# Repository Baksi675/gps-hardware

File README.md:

# GPS Tracking Device — Hardware

An electronic device built for GPS tracking. The project was made with KiCad.

For the firmware repository visit gps-firmware: https://github.com/Baksi675/gps-firmware

---

## Features

- STM32F401RE microcontroller.
- 32.768 kHz crystal oscillator for the internal RTC of the microcontroller.
- USB micro B connector to power the board and to provide USB based host - target runtime communication.
- USBLC6-2SC6 ESD protection diode network to protect the USB connector from ESD events.
- CH340C USB-UART converter IC to provide communication capabilities between host and target with a USB cable.
- LD30950PU33R LDO for 5 V to 3.3 V conversion.
- u-blox NEO-6M GPS module connected to the microcontroller via UART.
- U.FL antenna connector for the ceramic patch antenna.
- 3 V CR2032 coin cell for the internal RTC of the microcontroller.
- microSD card slot connected to the microcontroller via SPI.
- Three user button connectors.
- A 4 pin connector for the display (I2C).
- A 5 pin debug connector (SWD).
- A connector for an external GPS module in case the on-board module is not operational (UART).

---

## Demonstration playlist

https://www.youtube.com/watch?v=A6QJqgy0O1o&list=PLb_bXLsinHOQtkZ2X2QlIw-E_5eapHqGd

---

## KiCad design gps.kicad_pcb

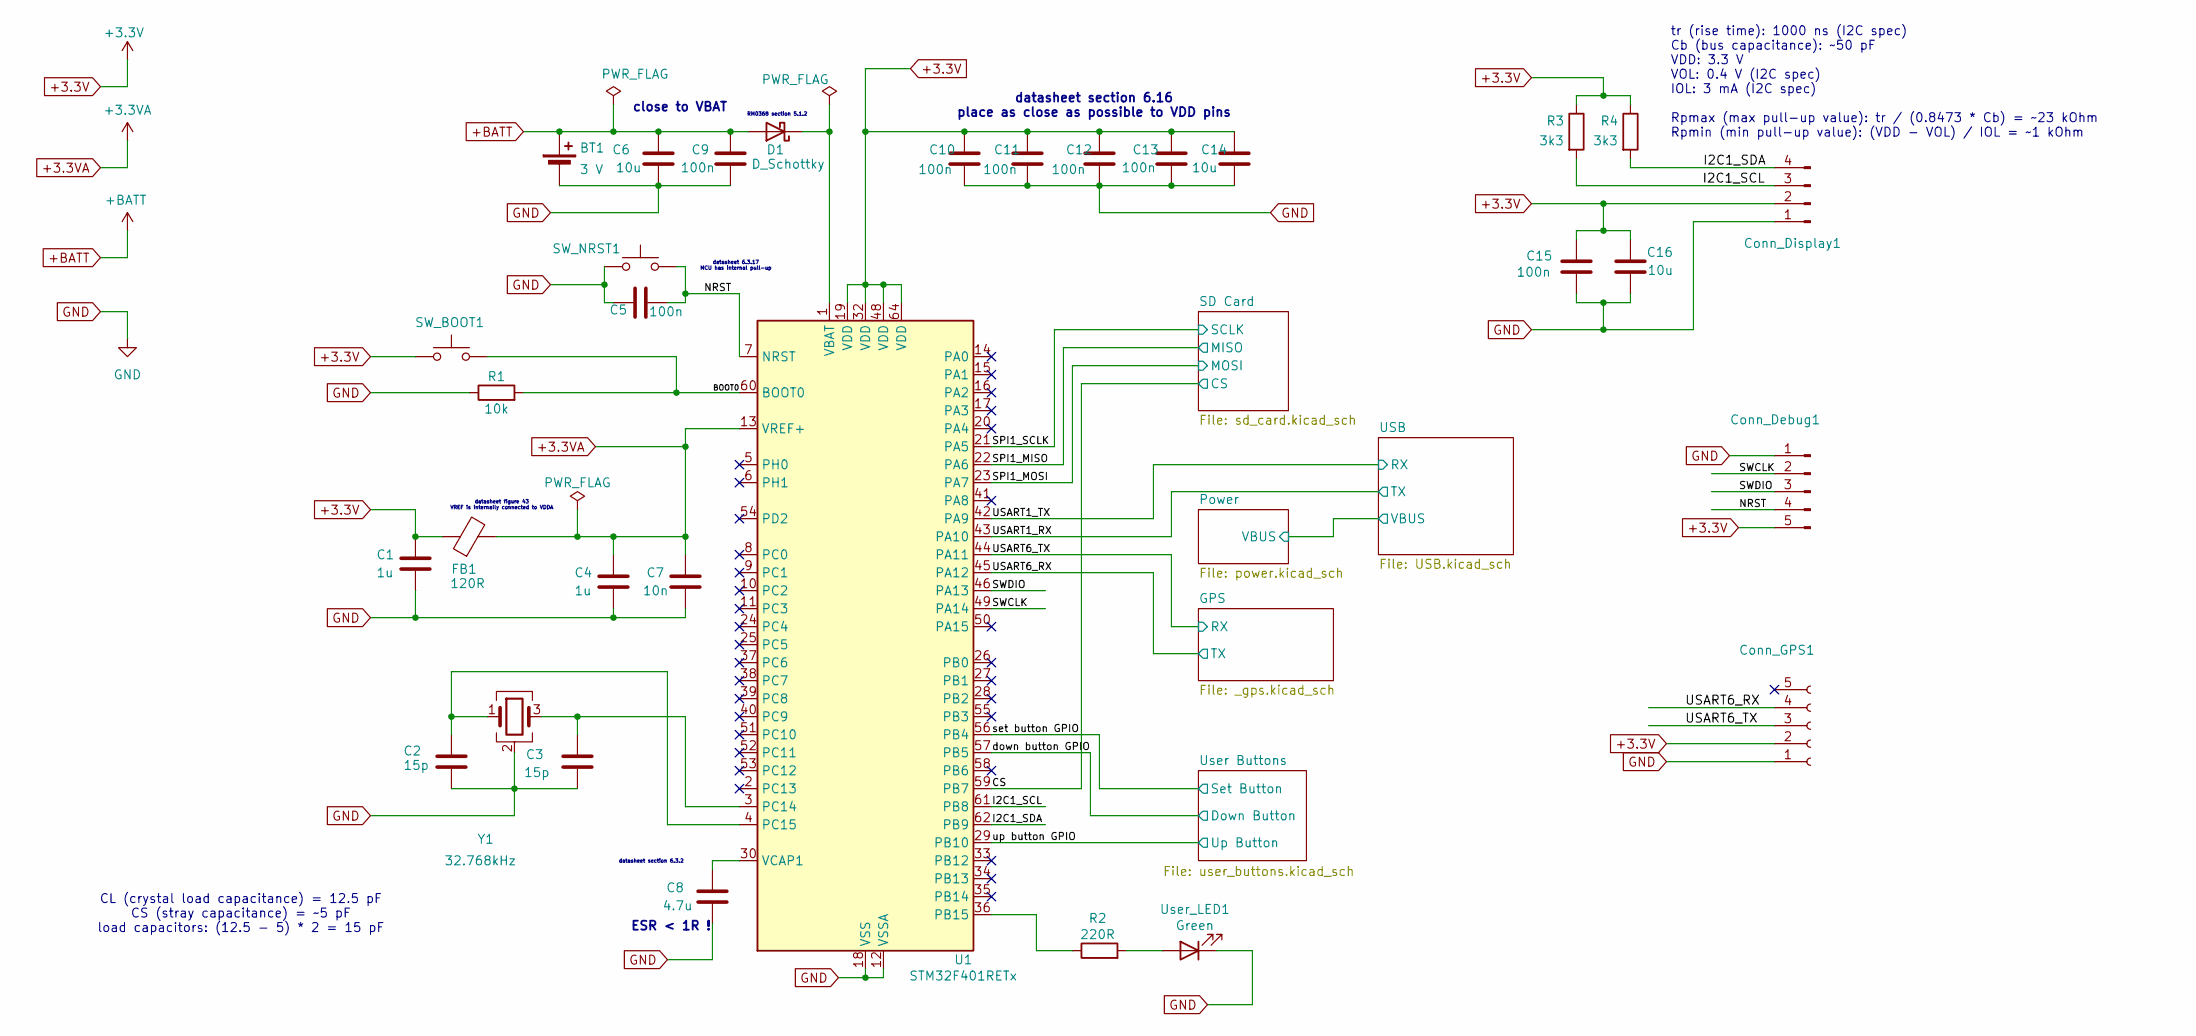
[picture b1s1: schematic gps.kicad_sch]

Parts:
BT1: 3 V; BatteryHolder_MYOUNG_BS-07-A1BJ001_CR2032
C1, C4: 1u; C_0603_1608Metric
C2, C3: 15p; C_0603_1608Metric
C5, C9, C10, C11, C12, C13, C15: 100n; C_0402_1005Metric
C6, C14, C16: 10u; C_0603_1608Metric
C7: 10n; C_0402_1005Metric
C8: 4.7u; C_0603_1608Metric
Conn_Debug1: Conn_01x05_Pin; PinHeader_1x05_P2.54mm_Vertical
Conn_Display1: Conn_01x04_Pin; PinHeader_1x04_P2.54mm_Vertical
Conn_GPS1: Conn_01x05_Socket; PinSocket_1x05_P2.54mm_Vertical
D1: D_Schottky; D_0603_1608Metric
FB1: 120R; L_0603_1608Metric
R1: 10k; R_0402_1005Metric
R2: 220R; R_0402_1005Metric
R3, R4: 3k3; R_0402_1005Metric
SW_BOOT1: SW_Push; SW_Push_1P1T_NO_E-Switch_TL3301NxxxxxG
SW_NRST1: SW_Push; SW_Push_1P1T_NO_E-Switch_TL3301NxxxxxG
U1: STM32F401RETx; LQFP-64_10x10mm_P0.5mm
User_LED1: Green; LED_0603_1608Metric
Y1: 32.768kHz; Crystal_SMD_SeikoEpson_MC306-4Pin_8.0x3.2mm

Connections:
+3.3V: C1.1, C10.1, C11.1, C12.1, C13.1, C14.1, C15.2, C16.2, Conn_Debug1.5, Conn_Display1.2, Conn_GPS1.2, FB1.1, R3.1, R4.1, SW_BOOT1.1, U1.19 (VDD), U1.32 (VDD), U1.48 (VDD), U1.64 (VDD); also elsewhere on the board
+3.3VA: C4.1, C7.1, FB1.2, U1.13 (VREF+)
+BATT: BT1.1 (+), C6.1, C9.1, D1.2 (A); also elsewhere on the board
/BOOT0: R1.2, SW_BOOT1.2, U1.60 (BOOT0)
/CS: U1.59 (PB7); also elsewhere on the board
/I2C1_SCL: Conn_Display1.3, R3.2, U1.61 (PB8)
/I2C1_SDA: Conn_Display1.4, R4.2, U1.62 (PB9)
/NRST: C5.2, Conn_Debug1.4, SW_NRST1.2, U1.7 (NRST)
/SPI1_MISO: U1.22 (PA6); also elsewhere on the board
/SPI1_MOSI: U1.23 (PA7); also elsewhere on the board
/SPI1_SCLK: U1.21 (PA5); also elsewhere on the board
/SWCLK: Conn_Debug1.2, U1.49 (PA14)
/SWDIO: Conn_Debug1.3, U1.46 (PA13)
/USART1_RX: U1.43 (PA10); also elsewhere on the board
/USART1_TX: U1.42 (PA9); also elsewhere on the board
/USART6_RX: Conn_GPS1.4, U1.45 (PA12); also elsewhere on the board
/USART6_TX: Conn_GPS1.3, U1.44 (PA11); also elsewhere on the board
/down button GPIO: U1.57 (PB5); also elsewhere on the board
/set button GPIO: U1.56 (PB4); also elsewhere on the board
/up button GPIO: U1.29 (PB10); also elsewhere on the board
GND: BT1.2 (-), C1.2, C2.2, C3.2, C4.2, C5.1, C6.2, C7.2, C8.2, C9.2, C10.2, C11.2, C12.2, C13.2, C14.2, C15.1, C16.1, Conn_Debug1.1, Conn_Display1.1, Conn_GPS1.1, R1.1, SW_NRST1.1, U1.12 (VSSA), U1.18 (VSS), U1.31 (VSS), U1.47 (VSS), U1.63 (VSS), User_LED1.1 (K), Y1.2 (G), Y1.4 (G); also elsewhere on the board
unnamed: D1.1 (K), U1.1 (VBAT)
unnamed: R2.1, U1.36 (PB15)
unnamed: C3.1, U1.3 (PC14), Y1.3
unnamed: C2.1, U1.4 (PC15), Y1.1
unnamed: C8.1, U1.30 (VCAP1)
unnamed: R2.2, User_LED1.2 (A)

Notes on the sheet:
CL (crystal load capacitance) = 12.5 pF CS (stray capacitance) = ~5 pF load capacitors: (12.5 - 5) * 2 = 15 pF
close to VBAT
datasheet figure 43 VREF is internally connected to VDDA
ESR < 1R !
datasheet section 6.3.2
datasheet section 6.16 place as close as possible to VDD pins
tr (rise time): 1000 ns (I2C spec) Cb (bus capacitance): ~50 pF VDD: 3.3 V VOL: 0.4 V (I2C spec) IOL: 3 mA (I2C spec) Rpmax (max pull-up value): tr / (0.8473 * Cb) = ~23 kOhm Rpmin (min pull-up value): (VDD - VOL) / IOL = ~1 kOhm
RM0368 section 5.1.2
datasheet 6.3.17 MCU has internal pull-up

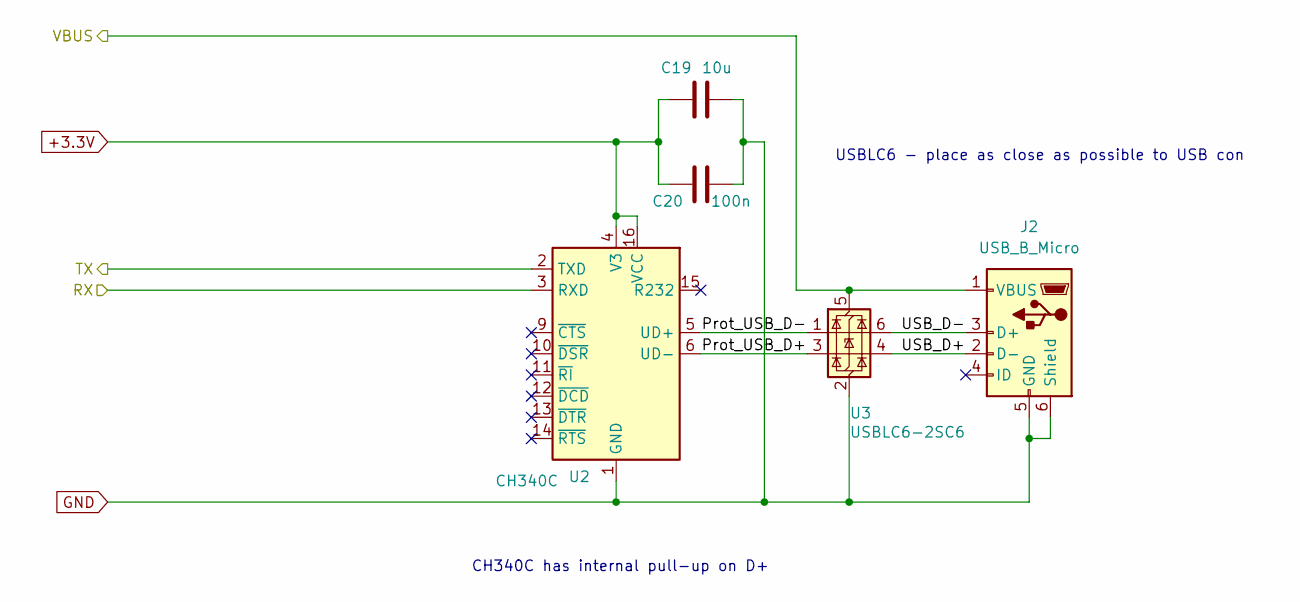
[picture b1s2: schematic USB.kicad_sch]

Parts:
C19: 10u; C_0603_1608Metric
C20: 100n; C_0402_1005Metric
J2: USB_B_Micro; USB_Micro-B_Amphenol_10118194-0001LF_Horizontal
U2: CH340C; SOIC-16_3.9x9.9mm_P1.27mm
U3: USBLC6-2SC6; SOT-23-6

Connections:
+3.3V: C19.1, C20.1, U2.4 (V3), U2.16 (VCC); also elsewhere on the board
/Power/VBUS: J2.1 (VBUS), U3.5 (VBUS); also elsewhere on the board
/USART1_RX: U2.2 (TXD); also elsewhere on the board
/USART1_TX: U2.3 (RXD); also elsewhere on the board
/USB/Prot_USB_D+: U2.6 (UD-), U3.3 (I/O2)
/USB/Prot_USB_D-: U2.5 (UD+), U3.1 (I/O1)
/USB/USB_D+: J2.2 (D-), U3.4 (I/O2)
/USB/USB_D-: J2.3 (D+), U3.6 (I/O1)
GND: C19.2, C20.2, J2.5 (GND), J2.6 (Shield), U2.1 (GND), U3.2 (GND); also elsewhere on the board

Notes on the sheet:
CH340C has internal pull-up on D+
USBLC6 - place as close as possible to USB con

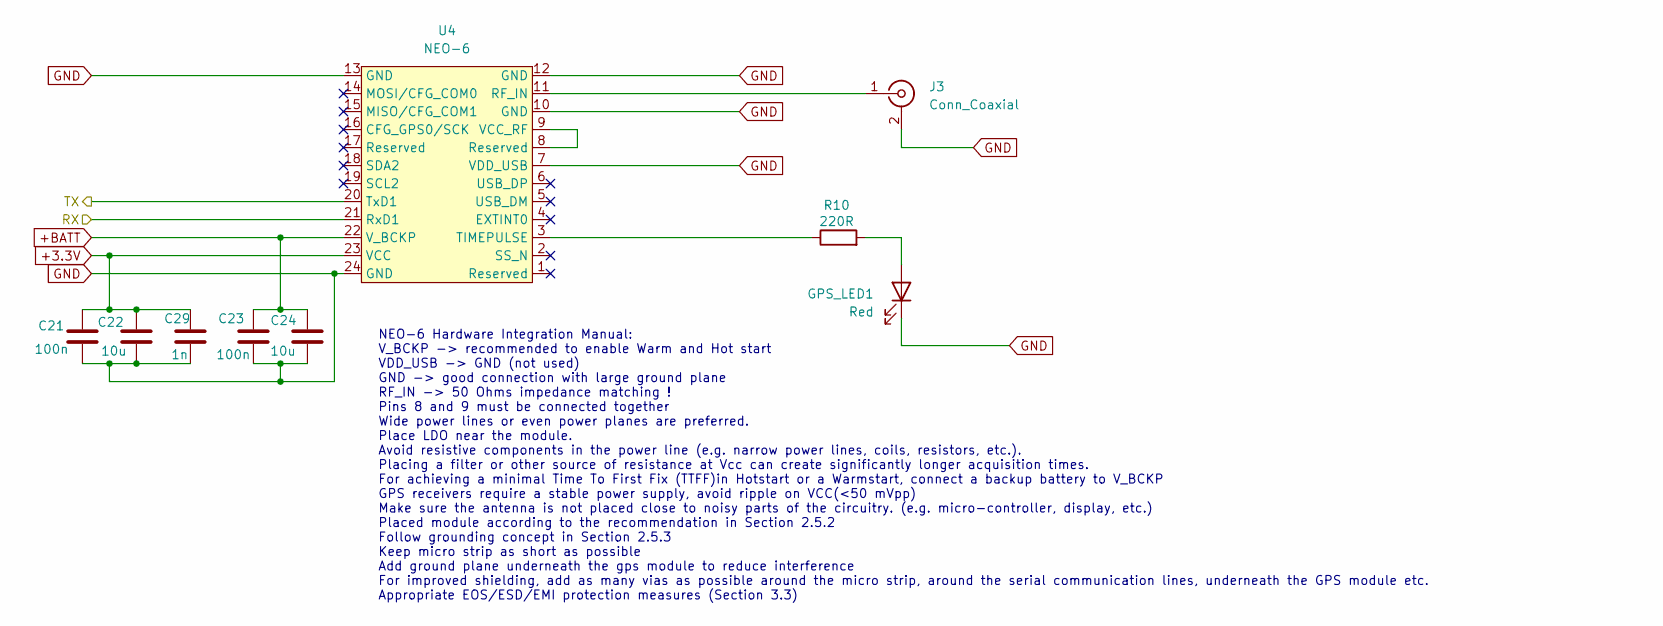
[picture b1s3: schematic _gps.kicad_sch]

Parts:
C21, C23: 100n; C_0402_1005Metric
C22, C24: 10u; C_0603_1608Metric
C29: 1n; C_0402_1005Metric
GPS_LED1: Red; LED_0603_1608Metric
J3: Conn_Coaxial; U.FL_Hirose_U.FL-R-SMT-1_Vertical
R10: 220R; R_0402_1005Metric
U4: NEO-6; ublox_NEO

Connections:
+3.3V: C21.1, C22.1, C29.1, U4.23 (VCC); also elsewhere on the board
+BATT: C23.1, C24.1, U4.22 (V_BCKP); also elsewhere on the board
/USART6_RX: U4.20 (TxD1); also elsewhere on the board
/USART6_TX: U4.21 (RxD1); also elsewhere on the board
GND: C21.2, C22.2, C23.2, C24.2, C29.2, GPS_LED1.1 (K), J3.2 (Ext), U4.7 (VDD_USB), U4.10 (GND), U4.12 (GND), U4.13 (GND), U4.24 (GND); also elsewhere on the board
unnamed: GPS_LED1.2 (A), R10.2
unnamed: J3.1 (In), U4.11 (RF_IN)
unnamed: R10.1, U4.3 (TIMEPULSE)
unnamed: U4.8 (Reserved), U4.9 (VCC_RF)

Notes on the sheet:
NEO-6 Hardware Integration Manual: V_BCKP -> recommended to enable Warm and Hot start VDD_USB -> GND (not used) GND -> good connection with large ground plane RF_IN -> 50 Ohms impedance matching ! Pins 8 and 9 must be connected together Wide power lines or even power planes are preferred. Place LDO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

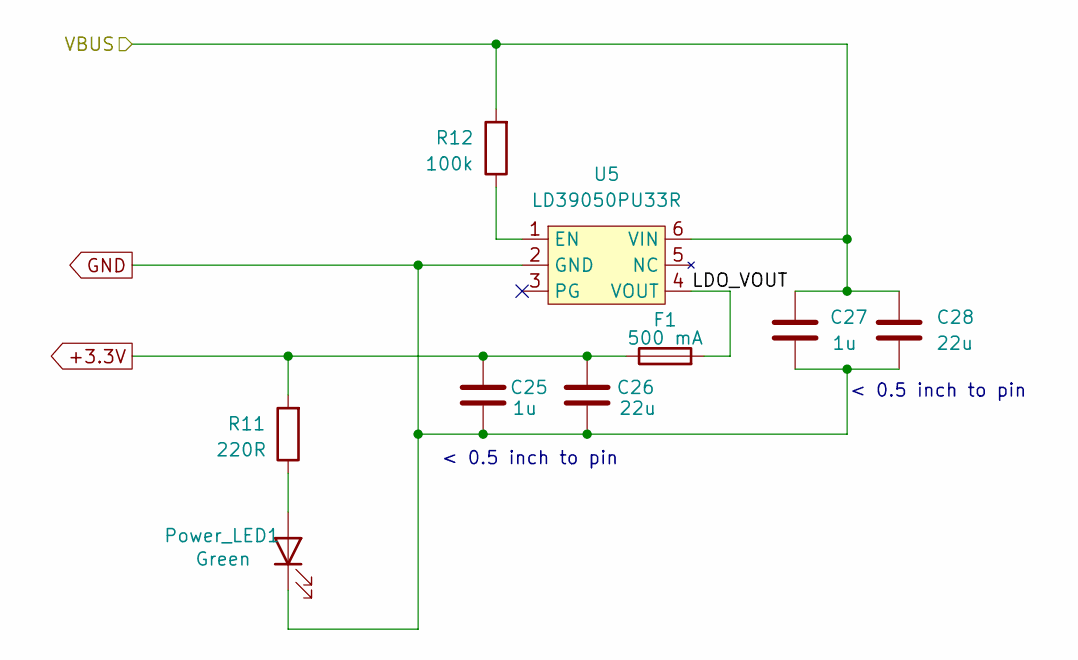
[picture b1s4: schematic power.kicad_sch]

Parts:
C25, C27: 1u; C_0603_1608Metric
C26, C28: 22u; C_0805_2012Metric
F1: 500 mA; Fuse_0603_1608Metric
Power_LED1: Green; LED_0603_1608Metric
R11: 220R; R_0402_1005Metric
R12: 100k; R_0402_1005Metric
U5: LD39050PU33R

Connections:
+3.3V: C25.1, C26.1, F1.1, R11.2; also elsewhere on the board
/Power/LDO_VOUT: F1.2, U5.4 (VOUT)
/Power/VBUS: C27.1, C28.1, R12.2, U5.6 (VIN); also elsewhere on the board
GND: C25.2, C26.2, C27.2, C28.2, Power_LED1.1 (K), U5.2 (GND); also elsewhere on the board
unnamed: Power_LED1.2 (A), R11.1
unnamed: R12.1, U5.1 (EN)

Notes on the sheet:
< 0.5 inch to pin

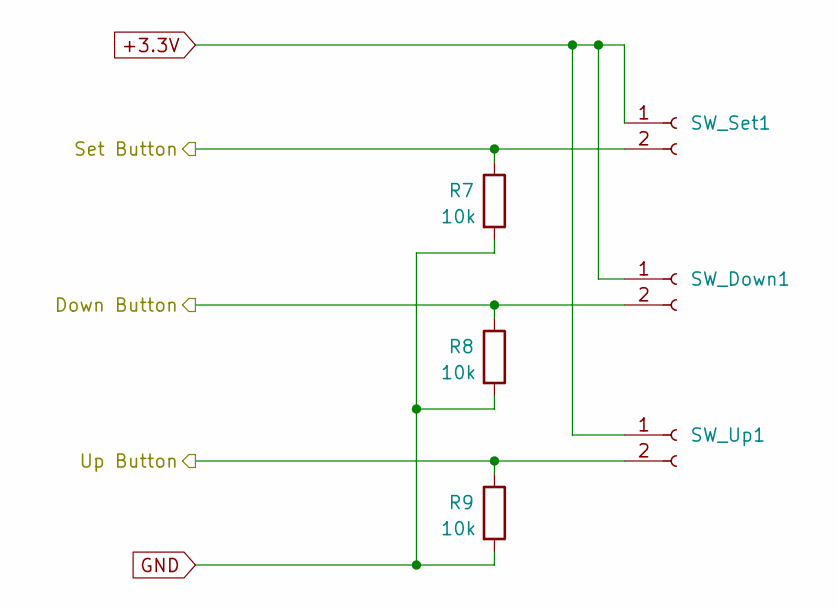
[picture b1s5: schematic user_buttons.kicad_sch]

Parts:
R7, R8, R9: 10k; R_0402_1005Metric
SW_Down1: Conn_01x02_Socket; PinSocket_1x02_P2.54mm_Vertical
SW_Set1: Conn_01x02_Socket; PinSocket_1x02_P2.54mm_Vertical
SW_Up1: Conn_01x02_Socket; PinSocket_1x02_P2.54mm_Vertical

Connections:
+3.3V: SW_Down1.1, SW_Set1.1, SW_Up1.1; also elsewhere on the board
/down button GPIO: R8.1, SW_Down1.2; also elsewhere on the board
/set button GPIO: R7.1, SW_Set1.2; also elsewhere on the board
/up button GPIO: R9.1, SW_Up1.2; also elsewhere on the board
GND: R7.2, R8.2, R9.2; also elsewhere on the board

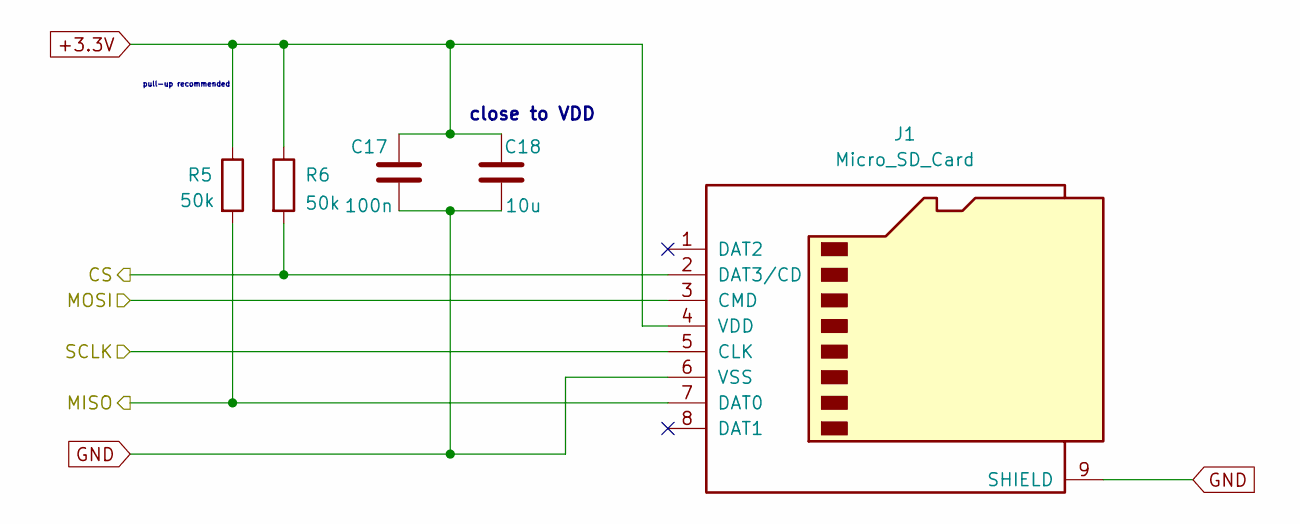
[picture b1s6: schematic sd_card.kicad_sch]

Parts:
C17: 100n; C_0402_1005Metric
C18: 10u; C_0603_1608Metric
J1: Micro_SD_Card; microSD_HC_Molex_104031-0811
R5, R6: 50k; R_0402_1005Metric

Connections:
+3.3V: C17.2, C18.2, J1.4 (VDD), R5.1, R6.1; also elsewhere on the board
/CS: J1.2 (DAT3/CD), R6.2; also elsewhere on the board
/SPI1_MISO: J1.7 (DAT0), R5.2; also elsewhere on the board
/SPI1_MOSI: J1.3 (CMD); also elsewhere on the board
/SPI1_SCLK: J1.5 (CLK); also elsewhere on the board
GND: C17.1, C18.1, J1.6 (VSS), J1.9 (SHIELD); also elsewhere on the board

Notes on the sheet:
pull-up recommended
close to VDD

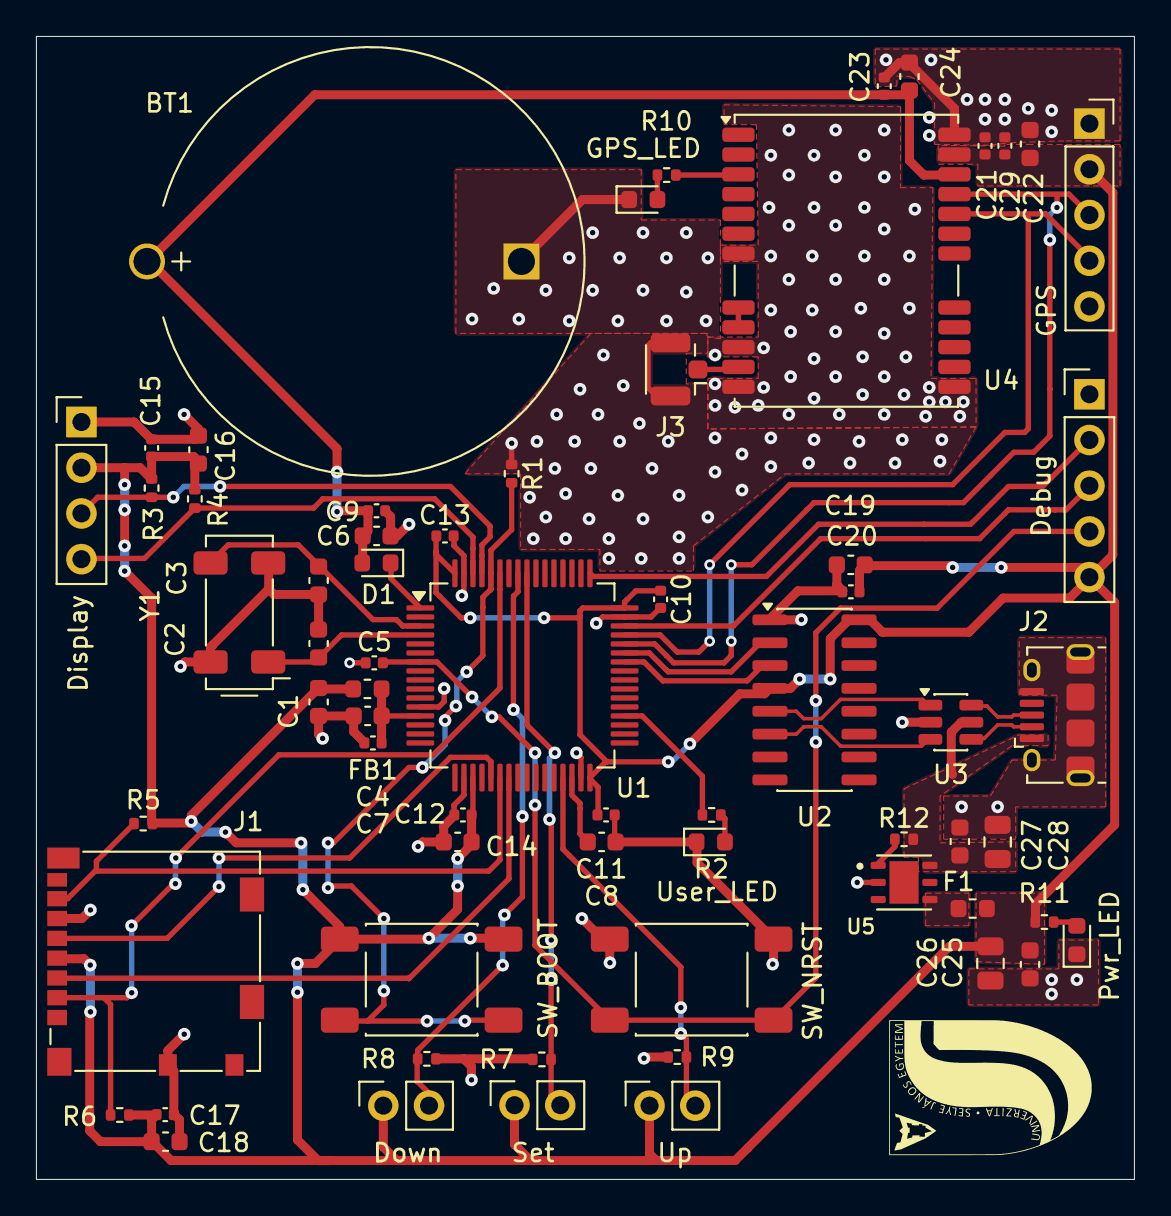
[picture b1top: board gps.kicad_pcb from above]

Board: 2 copper layers, 61.0 x 63.5 mm, 65 parts (0 on the bottom side), 39 nets.

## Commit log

2026-03-31 add kicad files
2026-03-31 add image
2026-03-31 add README.md and add image
